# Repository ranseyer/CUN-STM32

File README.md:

View this project on [CADLAB.io](https://cadlab.io/project/1060). 

# CUN-STM32
The MAPLE-CUL is an ARM based RF Transceiver w/wo LAN for 433 or 868 MHz

- based on the STM32 / MAPLE Microcontroller
- Up to 4 Transceiver-Modules
- 2 Free UARTs for other AddOns / Transceiver or so
- 1 UART for WLAN Connection or debugging

-a lot of HW-AddOns are availble

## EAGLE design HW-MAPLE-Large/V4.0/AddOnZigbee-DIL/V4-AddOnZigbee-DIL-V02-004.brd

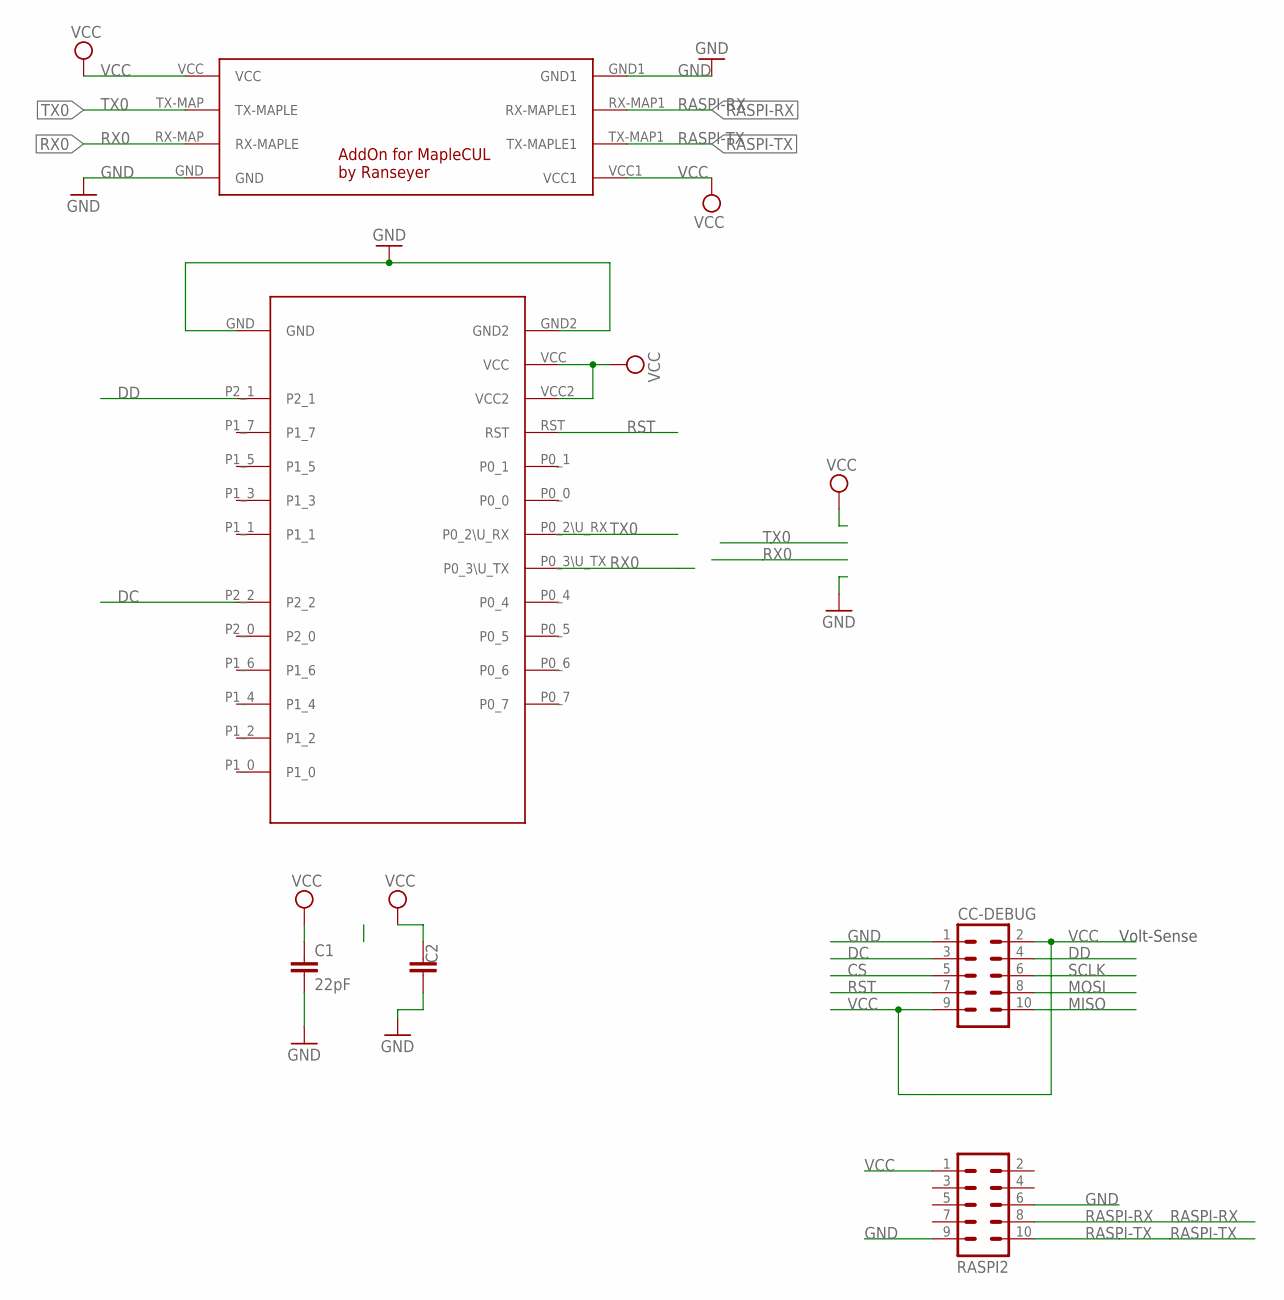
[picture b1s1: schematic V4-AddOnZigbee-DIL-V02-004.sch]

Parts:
C1: 22pF; C0805
C2: C-EUC1812; C1812
CC-DEBUG: CONN_05X2SHD_LOCK; 2X5-SHROUDED_LOCK
RASPI2: MA05-2
U$1: MAPLE-CUL-ADDON-V01; MAPLE-CUL-V01
U$3: CC2530_MODULE; CC2530_DIL

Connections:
CS: CC-DEBUG.5
DC: CC-DEBUG.3, U$3.P2_2
DD: CC-DEBUG.4, U$3.P2_1
GND: C1.2, C2.1, CC-DEBUG.1, RASPI2.6, RASPI2.9, U$1.GND, U$1.GND1, U$3.GND, U$3.GND2
MISO: CC-DEBUG.10
MOSI: CC-DEBUG.8
RASPI-RX: RASPI2.8, U$1.RX-MAP1 (RX-MAPLE1)
RASPI-TX: RASPI2.10, U$1.TX-MAP1 (TX-MAPLE1)
RST: CC-DEBUG.7, U$3.RST
RX0: U$1.RX-MAP (RX-MAPLE), U$3.P0_3\U_TX
SCLK: CC-DEBUG.6
TX0: U$1.TX-MAP (TX-MAPLE), U$3.P0_2\U_RX
VCC: C1.1, C2.2, CC-DEBUG.2, CC-DEBUG.9, RASPI2.1, U$1.VCC, U$1.VCC1, U$3.VCC, U$3.VCC2

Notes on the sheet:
Volt-Sense

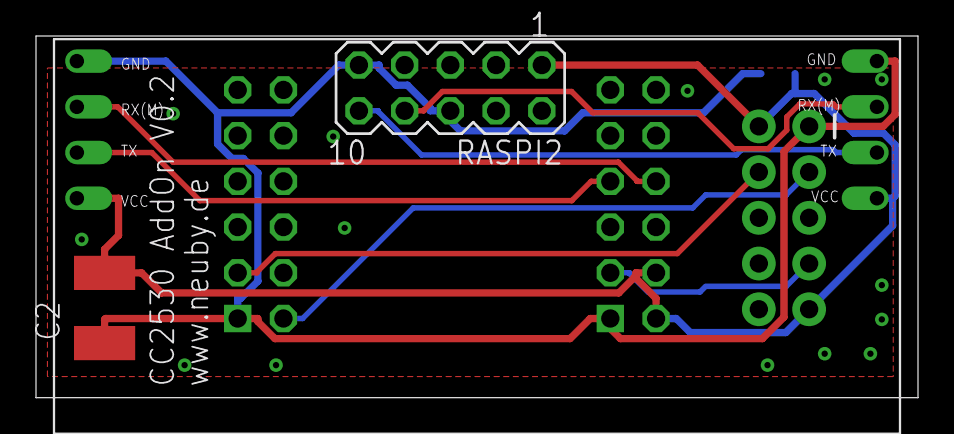
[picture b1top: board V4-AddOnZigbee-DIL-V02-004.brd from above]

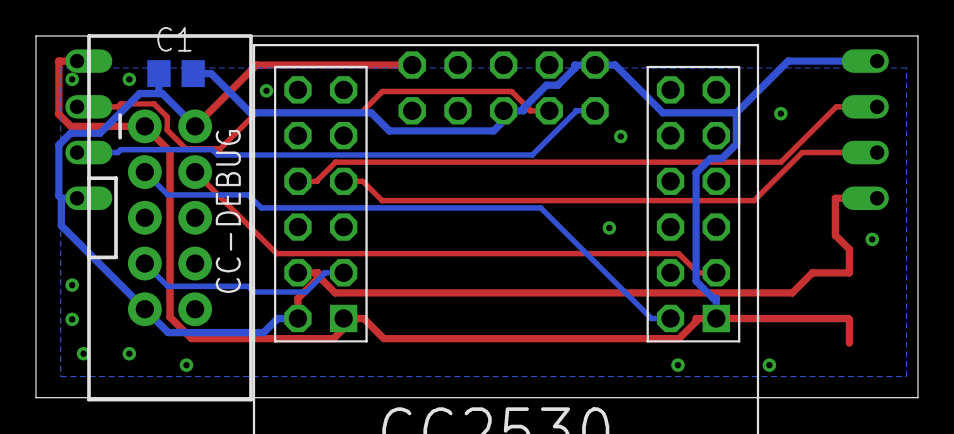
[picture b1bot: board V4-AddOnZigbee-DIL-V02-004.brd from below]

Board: 2 copper layers, 49.0 x 20.1 mm, 6 parts (3 on the bottom side), 9 nets.

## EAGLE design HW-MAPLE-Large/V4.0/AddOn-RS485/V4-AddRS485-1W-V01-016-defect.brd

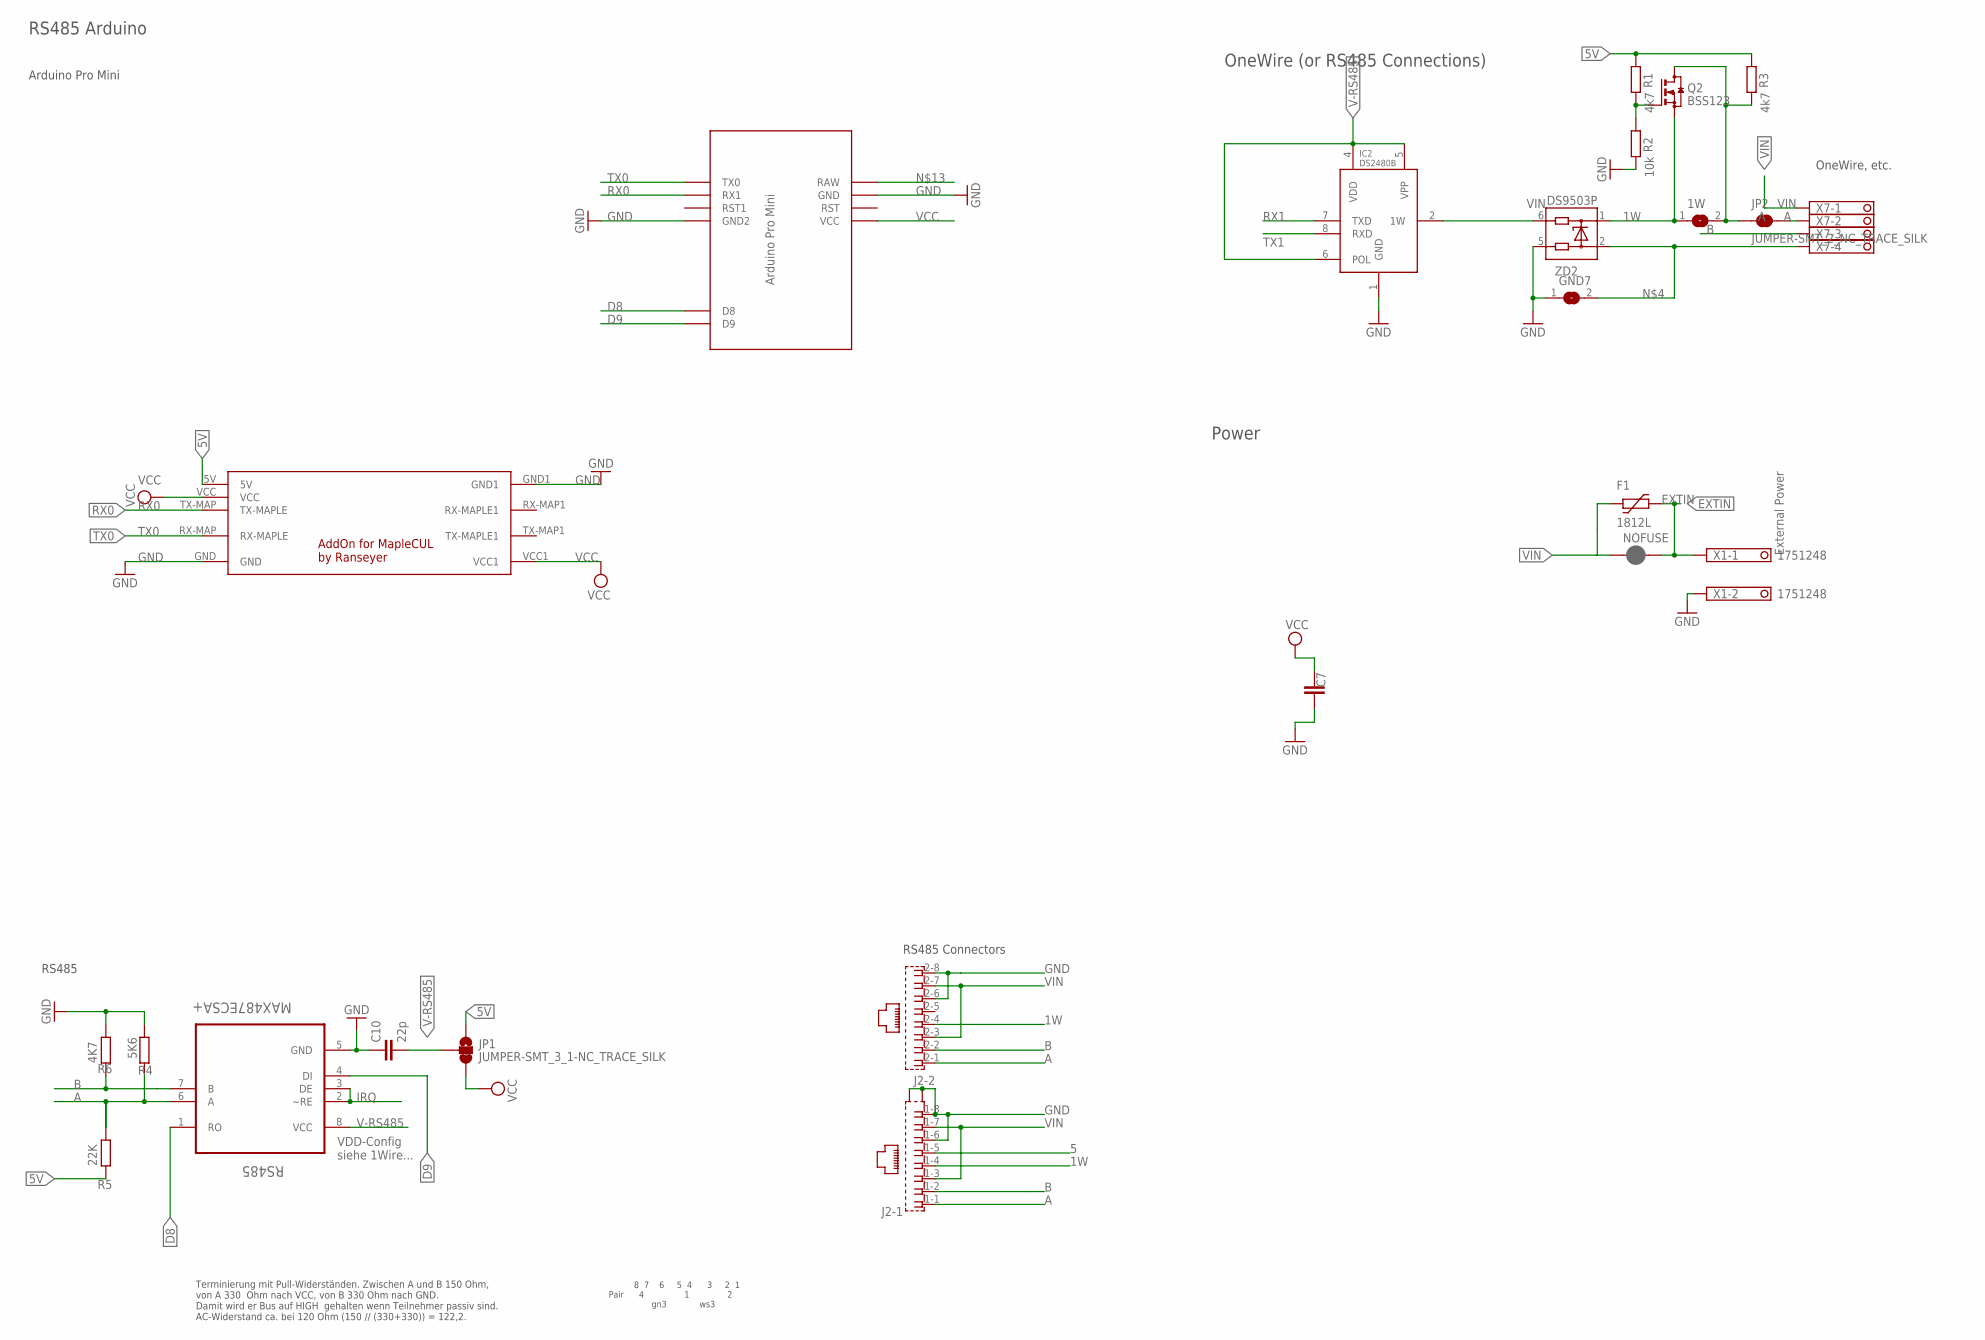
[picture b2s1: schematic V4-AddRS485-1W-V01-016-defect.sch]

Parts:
1W: SJ
C7: C-EUC1812; C1812
C10: 22p; C0805
F1: 1812L
GND7: SJ
IC2: DS2480B; SO08
J2: RJ45_2X_S
JP1: JUMPER-SMT_3_1-NC_TRACE_SILK; SMT-JUMPER_3_1-NC_TRACE_SILK
JP2: JUMPER-SMT_2_NC_TRACE_SILK; SMT-JUMPER_2_NC_TRACE_SILK
NOFUSE: JUMPER-SMT_2_NC_PASTE_NO-SILK; SMT-JUMPER_2_NC_PASTE_NO-SILK
Q2: BSS123; SOT23
R1, R3: 4k7; R0805
R2: 10k; R0805
R4: 5K6; R0805
R5: 22K; R0805
R6: 4K7; R0805
RS485: MAX487ECSA+; SOIC127P600X175-8N
U$2: MAPLE-CUL-ADDON-V01; MAPLE-CUL-V01
U$3: MARTIN-PRO-MINI-RS485
X1: 1751248
X7: 1751264
ZD2: DS9503P; TSOC6

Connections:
1W: 1W.1, J2.1-4 (4), J2.2-4 (4), Q2.2 (S), ZD2.1
5: J2.1-5 (5)
5V: JP1.1, R1.1, R3.1, R5.1, U$2.5V
A: 1W.2, J2.1-1 (1), J2.2-1 (1), JP2.1, JP2.2, Q2.3 (D), R3.2, R4.2, R5.2, RS485.6 (A), X7.2
B: J2.1-2 (2), J2.2-2 (2), R6.1, RS485.7 (B), X7.3
D8: RS485.1 (RO), U$3.D8
D9: RS485.4 (DI), U$3.D9
EXTIN: F1.P$2 (2), NOFUSE.2, X1.1
GND: C7.1, C10.1, GND7.1, IC2.1 (GND), J2.1-6 (6), J2.1-8 (8), J2.2-6 (6), J2.2-8 (8), J2.G1 (S2), J2.G3 (S1), R2.2, R4.1, R6.2, RS485.5 (GND), U$2.GND, U$2.GND1, U$3.GND, U$3.GND1 (GND2), X1.2, ZD2.5
IRQ: RS485.2 (~RE), RS485.3 (DE)
unnamed: C10.2, JP1.2
unnamed: IC2.2 (1W), ZD2.6
unnamed: GND7.2, X7.4, ZD2.2
unnamed: Q2.1 (G), R1.2, R2.1
RX0: U$2.TX-MAP (TX-MAPLE), U$3.RX1
RX1: IC2.7 (TXD)
TX0: U$2.RX-MAP (RX-MAPLE), U$3.TX0
TX1: IC2.8 (RXD)
V-RS485: IC2.4 (VDD), IC2.5 (VPP), IC2.6 (POL), RS485.8 (VCC)
VCC: C7.2, JP1.3, U$2.VCC, U$2.VCC1, U$3.VCC
VIN: F1.P$1 (1), J2.1-3 (3), J2.1-7 (7), J2.2-3 (3), J2.2-7 (7), NOFUSE.1, X7.1

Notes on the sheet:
External Power
8 7 6 5 4 3 2 1 Pair 4 1 2 gn3 ws3
RS485 Connectors
OneWire, etc.
Arduino Pro Mini
RS485
VDD-Config siehe 1Wire...
Terminierung mit Pull-Widerständen. Zwischen A und B 150 Ohm, von A 330 Ohm nach VCC, von B 330 Ohm nach GND. Damit wird er Bus auf HIGH gehalten wenn Teilnehmer passiv sind. AC-Widerstand ca. bei 120 Ohm (150 // (330+330)) = 122,2.
OneWire (or RS485 Connections)
RS485 Arduino
Power

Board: 2 copper layers, 23 parts (4 on the bottom side), 18 nets, no tracks yet.

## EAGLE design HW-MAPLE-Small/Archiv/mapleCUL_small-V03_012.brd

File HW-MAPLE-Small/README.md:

Cases: 

https://www.thingiverse.com/thing:4290984

https://www.thingiverse.com/thing:4286521

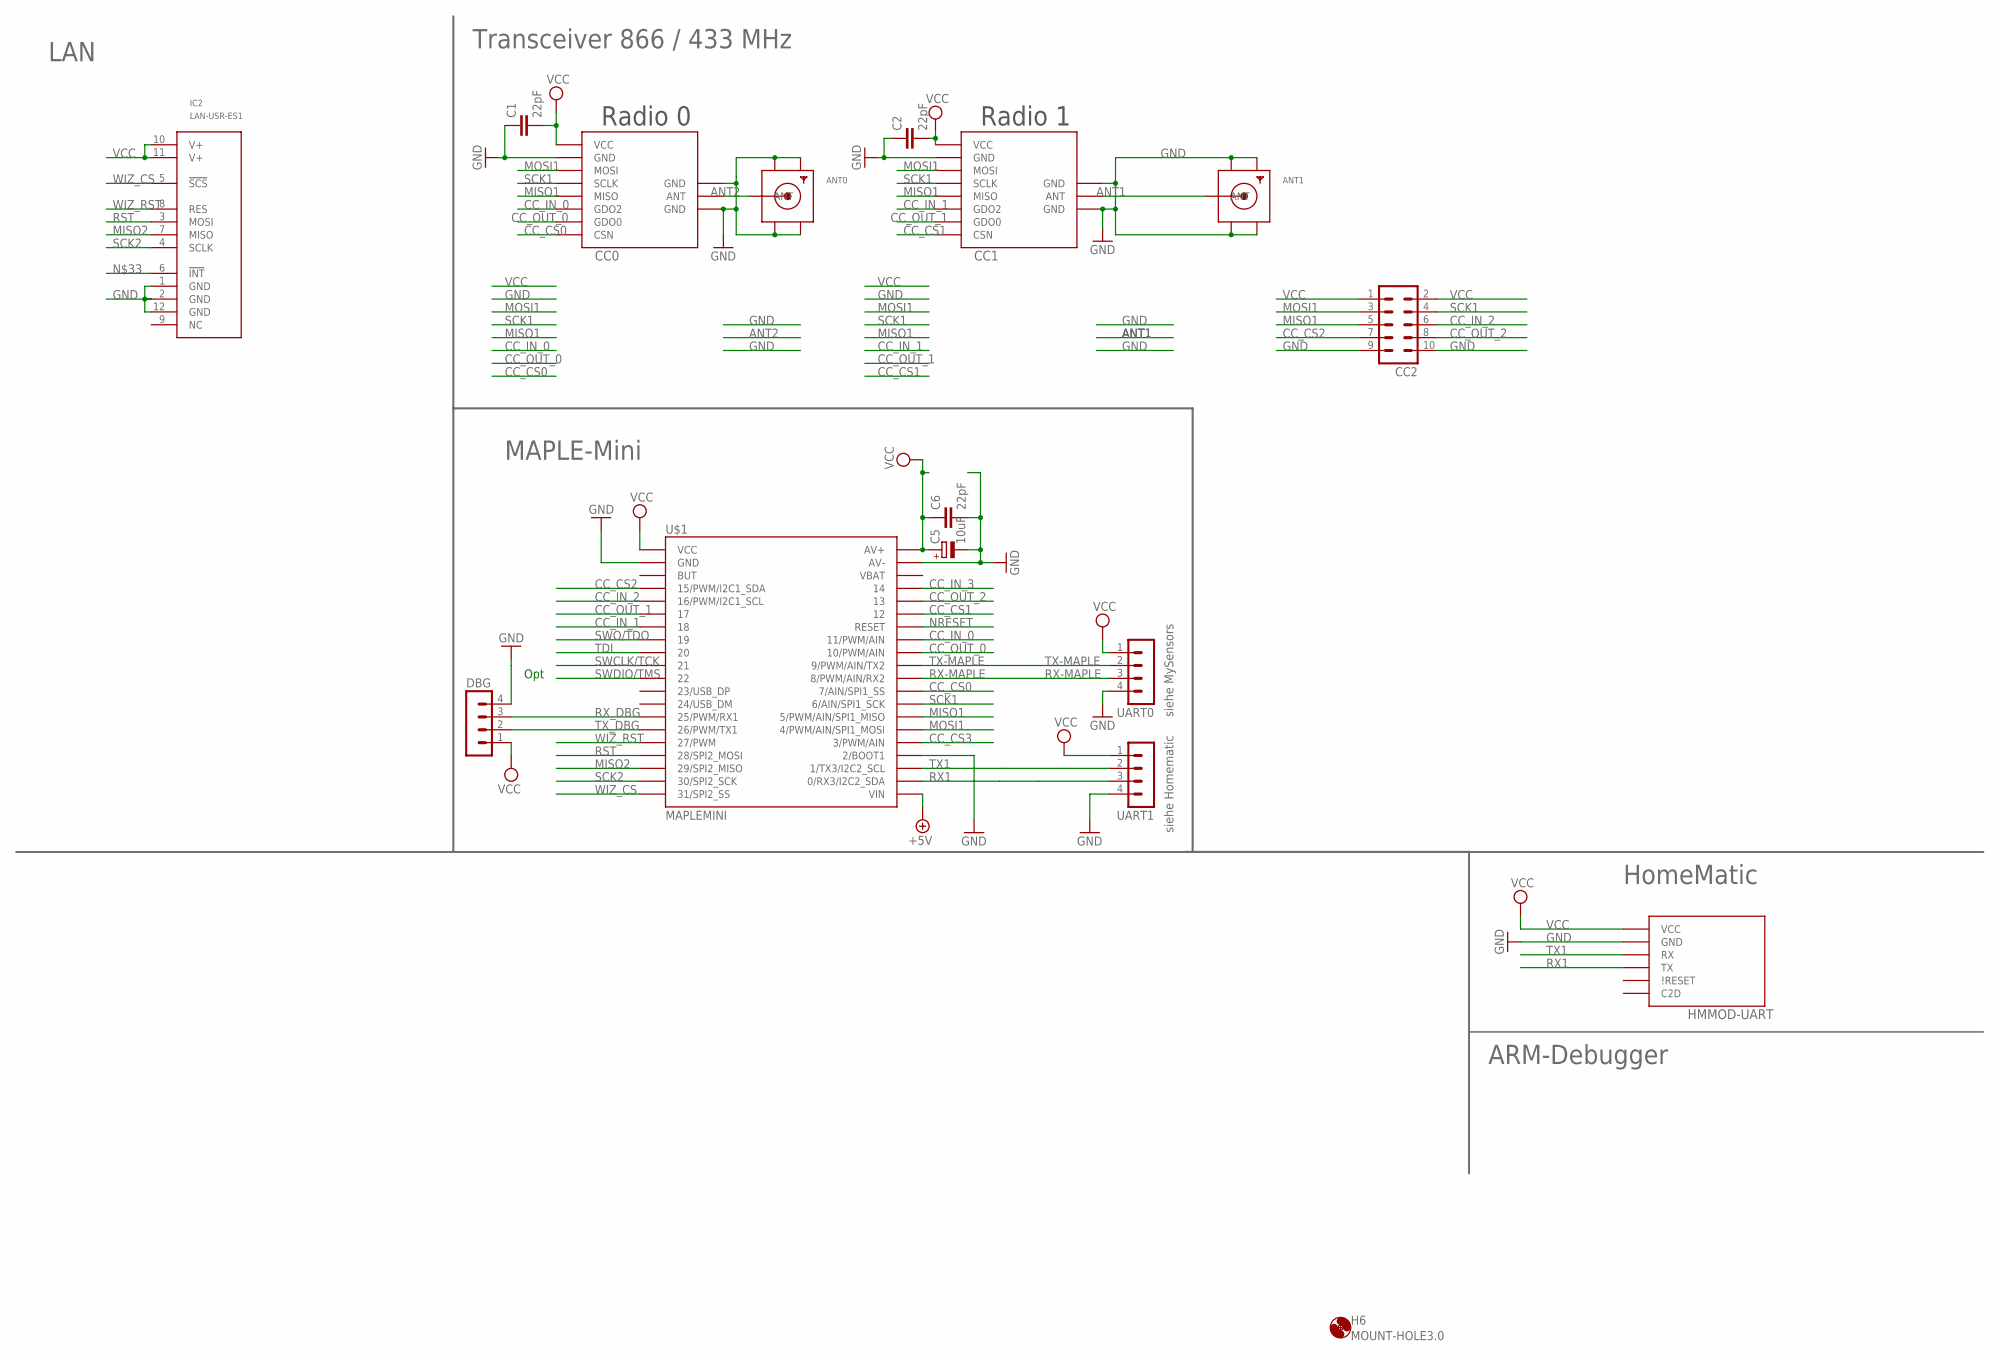
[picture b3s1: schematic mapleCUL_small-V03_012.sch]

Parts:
ANT0, ANT1: SMACONNECTOR_EDGE_UFL; SMA_EDGELAUNCH_UFL
C1, C2, C6: 22pF; C0805
C5: 10uF; R/2012-12W
CC0: CC1101; CC1101_MODULE1_SMD
CC1: CC1101_MODULE1SMD; CC1101_MODULE1_SMD
CC2: MA05-2
DBG: MA04-1
H6: MOUNT-HOLE3.0; 3,0
HMMOD-UART: HM-MOD-UARTDIL; HM-MOD-UART-DIL
IC2: LAN-USR-ES1; USR-ES1
U$1: MAPLEMINI; 20-DIP
UART0, UART1: MA04-1

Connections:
+5V: U$1.21 (VIN)
ANT1: ANT1.P (ANT), CC1.ANT
ANT2: ANT0.P (ANT), CC0.ANT
CC_CS0: CC0.CSN, U$1.29 (7/AIN/SPI1_SS)
CC_CS1: CC1.CSN, U$1.35 (12)
CC_CS2: CC2.7, U$1.4 (15/PWM/I2C1_SDA)
CC_CS3: U$1.25 (3/PWM/AIN)
CC_IN_0: CC0.GDO2, U$1.33 (11/PWM/AIN)
CC_IN_1: CC1.GDO2, U$1.7 (18)
CC_IN_2: CC2.6, U$1.5 (16/PWM/I2C1_SCL)
CC_IN_3: U$1.37 (14)
CC_OUT_0: CC0.GDO0, U$1.32 (10/PWM/AIN)
CC_OUT_1: CC1.GDO0, U$1.6 (17)
CC_OUT_2: CC2.8, U$1.36 (13)
GND: ANT0.GND@1 (GND1), ANT0.GND@2 (GND2), ANT0.GND@3 (GND3), ANT0.GND@4 (GND4), ANT1.GND@1 (GND1), ANT1.GND@2 (GND2), ANT1.GND@3 (GND3), ANT1.GND@4 (GND4), C1.1, C2.1, C5.-, C6.2, CC0.GND@0 (GND), CC0.GND@1 (GND), CC0.GND@2 (GND), CC1.GND@0 (GND), CC1.GND@1 (GND), CC1.GND@2 (GND), CC2.9, CC2.10, DBG.4, HMMOD-UART.2 (GND), IC2.1 (GND), IC2.2 (GND), IC2.12 (GND), U$1.2 (GND), U$1.24 (2/BOOT1), U$1.39 (AV-), UART0.4, UART1.4
MISO1: CC0.MISO, CC1.MISO, CC2.5, U$1.27 (5/PWM/AIN/SPI1_MISO)
MISO2: IC2.7 (MISO), U$1.18 (29/SPI2_MISO)
MOSI1: CC0.MOSI, CC1.MOSI, CC2.3, U$1.26 (4/PWM/AIN/SPI1_MOSI)
NRESET: U$1.34 (RESET)
RST: IC2.3 (MOSI), U$1.17 (28/SPI2_MOSI)
RX1: HMMOD-UART.5 (TX), U$1.22 (0/RX3/I2C2_SDA), UART1.3
RX-MAPLE: U$1.30 (8/PWM/AIN/RX2), UART0.3
RX_DBG: DBG.3, U$1.14 (25/PWM/RX1)
SCK1: CC0.SCLK, CC1.SCLK, CC2.4, U$1.28 (6/AIN/SPI1_SCK)
SCK2: IC2.4 (SCLK), U$1.19 (30/SPI2_SCK)
SWCLK/TCK: U$1.10 (21)
SWDIO/TMS: U$1.11 (22)
SWO/TDO: U$1.8 (19)
TDI: U$1.9 (20)
TX1: HMMOD-UART.6 (RX), U$1.23 (1/TX3/I2C2_SCL), UART1.2
TX-MAPLE: U$1.31 (9/PWM/AIN/TX2), UART0.2
TX_DBG: DBG.2, U$1.15 (26/PWM/TX1)
VCC: C1.2, C2.2, C5.+, C6.1, CC0.VCC, CC1.VCC, CC2.1, CC2.2, DBG.1, HMMOD-UART.1 (VCC), IC2.10 (V+), IC2.11 (V+), U$1.1 (VCC), U$1.40 (AV+), UART0.1, UART1.1
WIZ_CS: IC2.5 (!SCS!), U$1.20 (31/SPI2_SS)
WIZ_RST: IC2.8 (RES), U$1.16 (27/PWM)

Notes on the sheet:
Radio 1
Radio 0
Opt
siehe Homematic
siehe MySensors
HomeMatic
MAPLE-Mini
Transceiver 866 / 433 MHz
LAN
ARM-Debugger

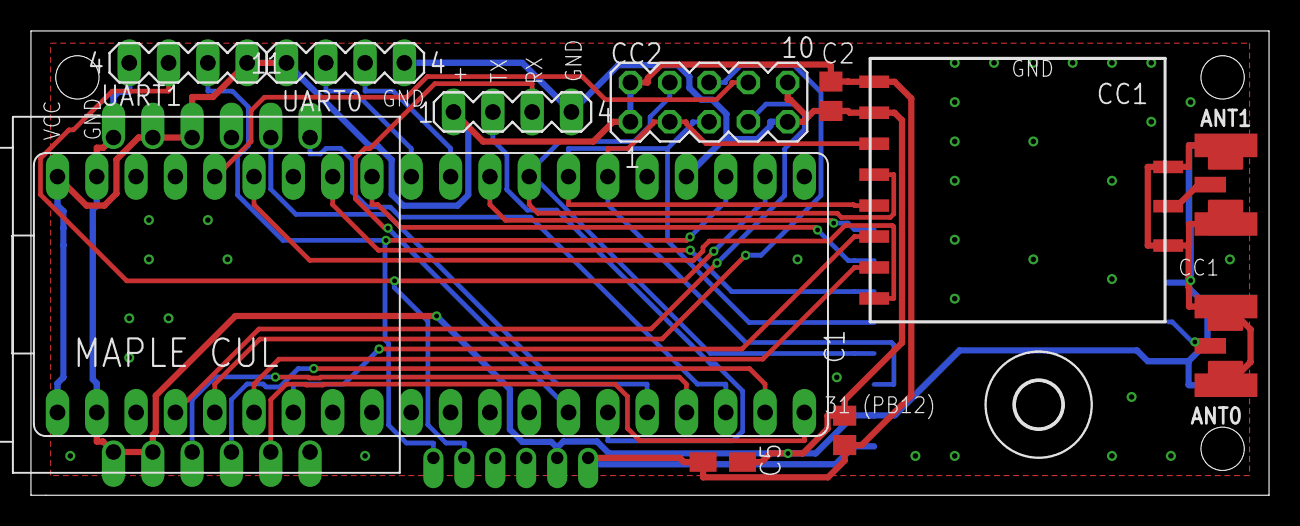
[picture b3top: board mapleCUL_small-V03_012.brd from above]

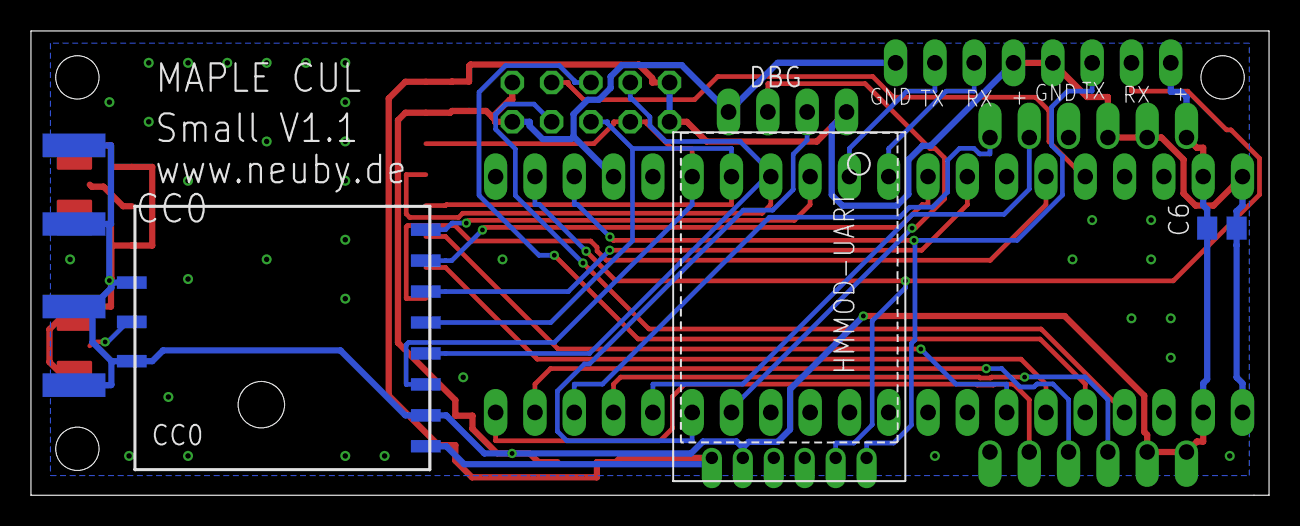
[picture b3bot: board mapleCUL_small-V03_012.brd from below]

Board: 2 copper layers, 80.0 x 30.0 mm, 16 parts (3 on the bottom side), 27 nets.

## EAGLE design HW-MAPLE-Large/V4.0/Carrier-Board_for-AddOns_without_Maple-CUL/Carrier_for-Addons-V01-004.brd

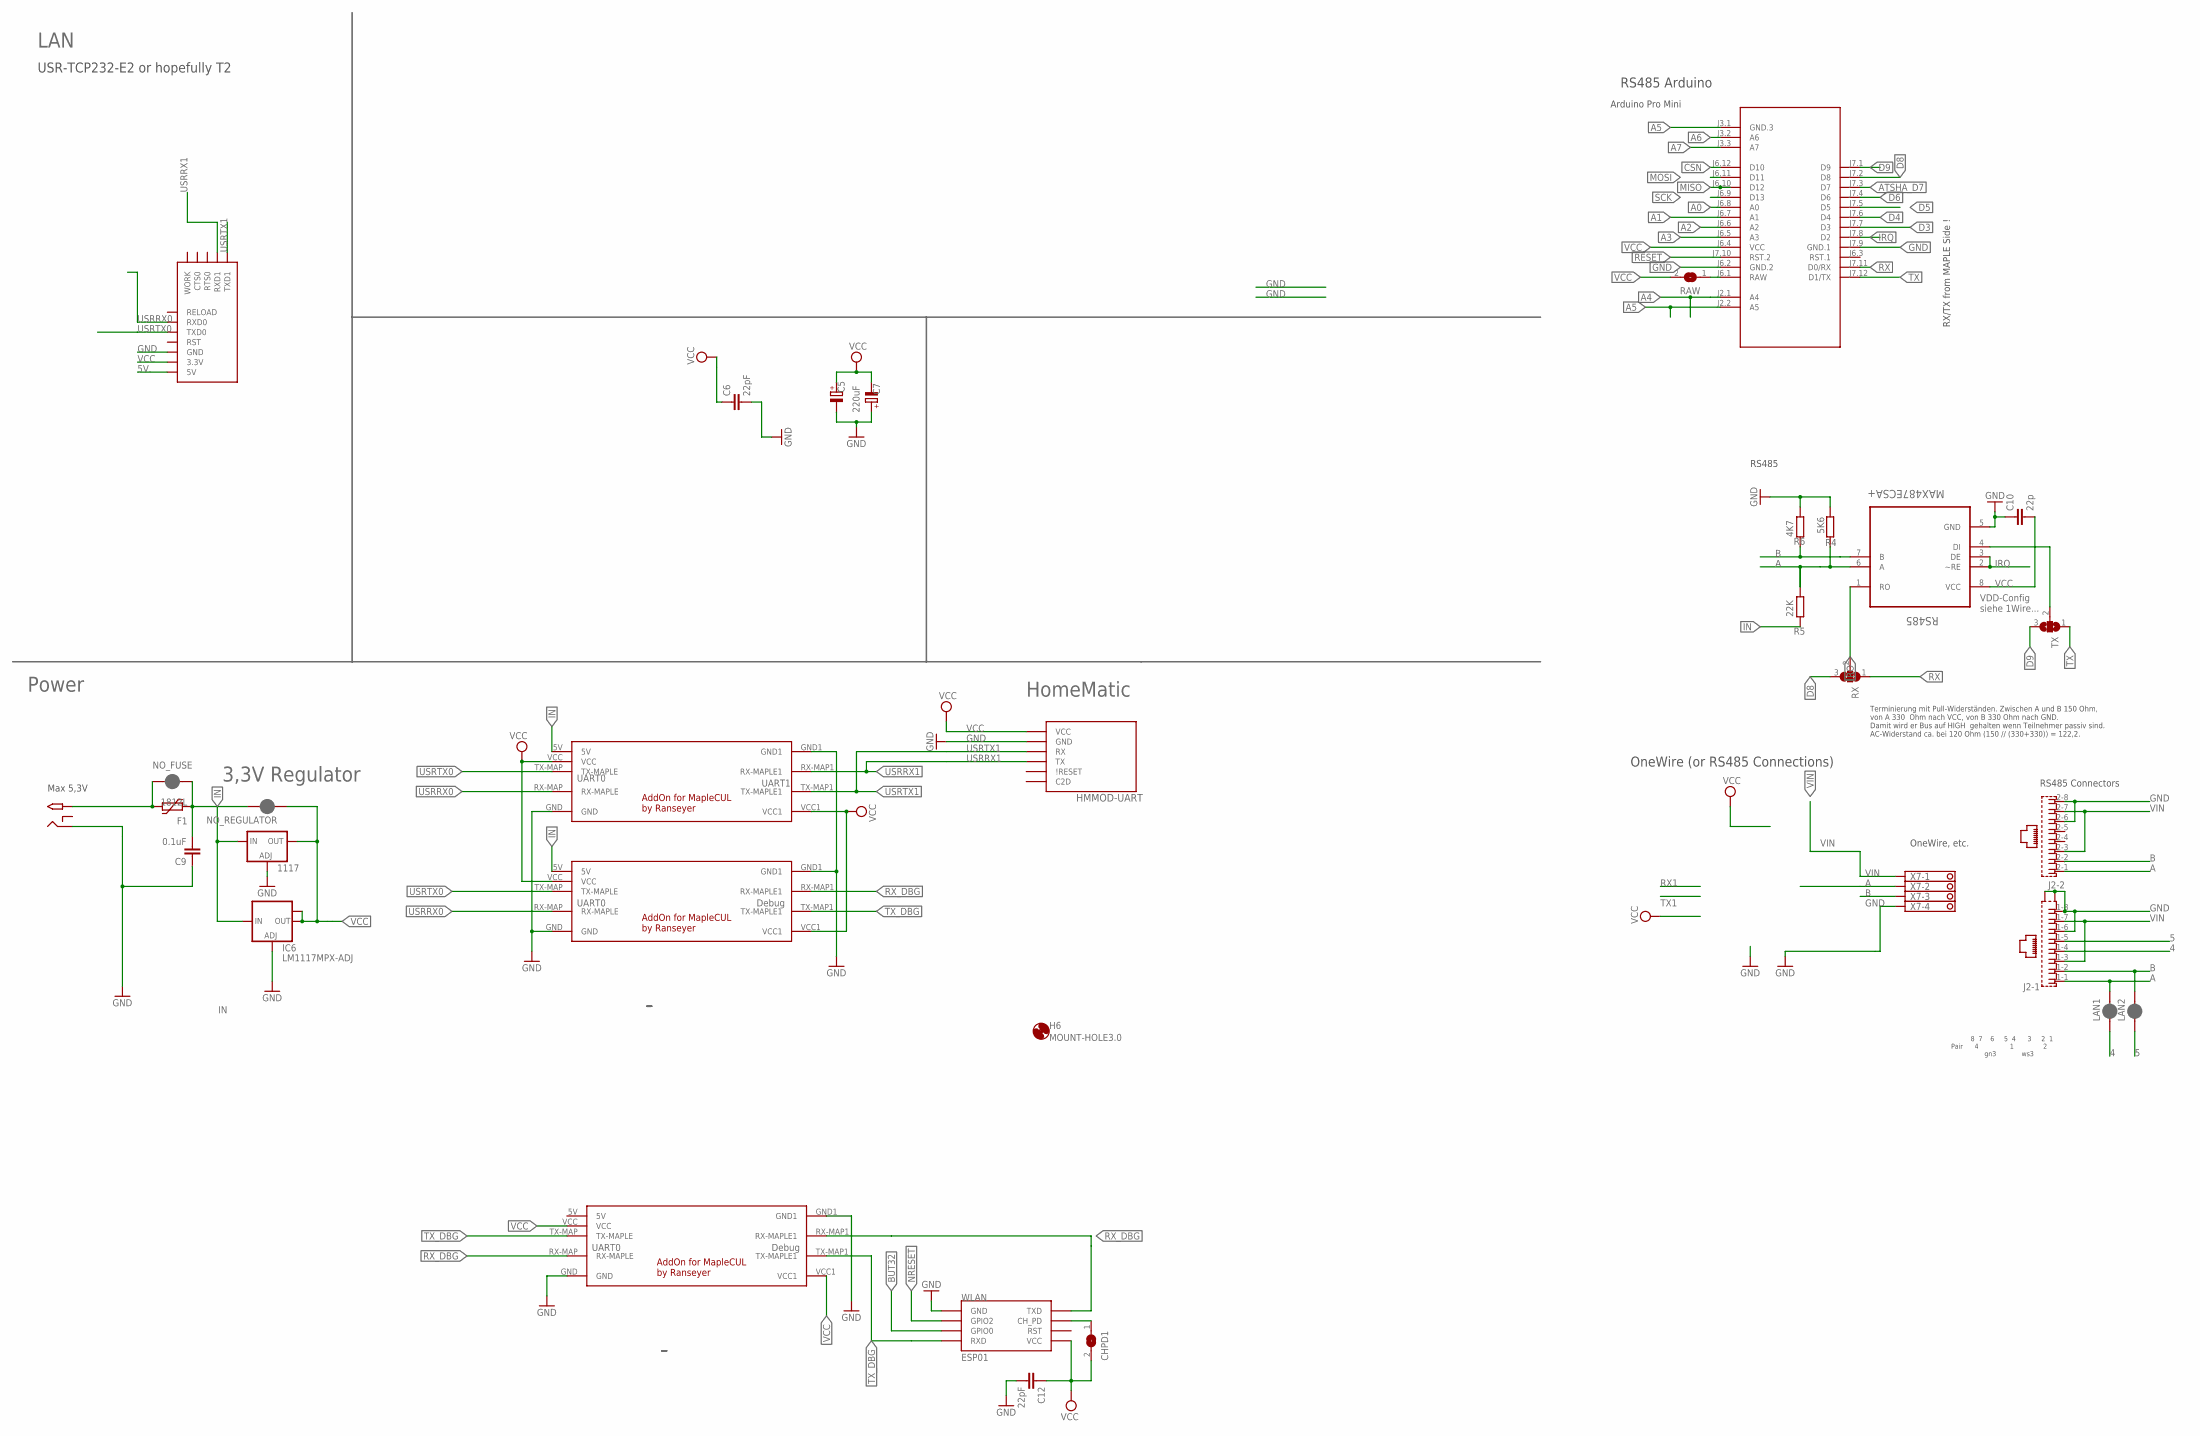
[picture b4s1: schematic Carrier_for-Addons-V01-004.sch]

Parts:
1117: LD117ADT50TR; DPACK
C5: 220uF; E5-8,5
C6, C12: 22pF; C0805
C7: CPOL-EUSMCE; SMC_E
C9: 0.1uF; C1206
C10: 22p; C0805
CHPD1: SJ
F1: 1812L
H6: MOUNT-HOLE3.0; 3,0
HMMOD-UART: HM-MOD-UARTDIL; HM-MOD-UART-DIL
IC6: LM1117MPX-ADJ; SOT223
J2: RJ45_2X_S
LAN1, LAN2: JUMPER-SMT_2_NC_PASTE_SILK; SMT-JUMPER_2_NC_PASTE_SILK
M1: ARDUINO-PRO-MINI-3.3V#NP; ARDUINO-PRO-MINI#NP
NO_FUSE: JUMPER-SMT_2_NC_PASTE_NO-SILK; SMT-JUMPER_2_NC_PASTE_NO-SILK
NO_REGULATOR: JUMPER-SMT_2_NC_PASTE_NO-SILK; SMT-JUMPER_2_NC_PASTE_NO-SILK
R4: 5K6; R0805
R5: 22K; R0805
R6: 4K7; R0805
RAW: SJ
RS485: MAX487ECSA+; SOIC127P600X175-8N
RX: SJ2W; SJ_2
TX: SJ2W; SJ_2
U$1, U$3, U$4: MAPLE-CUL-ADDON-V01; MAPLE-CUL-V01
U$2: 2.1MMJACKTHM; PJ-102A
U$5: USR-TCP232-E2
WLAN: ESP01
X7: 1751264

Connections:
4: J2.1-4 (4), LAN1.1
5: J2.1-5 (5), LAN2.1
5V.: U$5.5V
A: J2.1-1 (1), J2.2-1 (1), LAN1.2, R4.2, R5.2, RS485.6 (A), X7.2
A0: M1.J6.8 (A0)
A1: M1.J6.7 (A1)
A2: M1.J6.6 (A2)
A3: M1.J6.5 (A3)
A4: M1.J2.1 (A4)
A5: M1.J2.2 (A5), M1.J3.1 (GND.3)
A6: M1.J3.2 (A6)
A7: M1.J3.3 (A7)
ATSHA_D7: M1.J7.3 (D7)
B: J2.1-2 (2), J2.2-2 (2), LAN2.2, R6.1, RS485.7 (B), X7.3
BUT32: WLAN.GPIO0
CSN: M1.J6.12 (D10)
D3: M1.J7.7 (D3)
D4: M1.J7.6 (D4)
D5: M1.J7.5 (D5)
D6: M1.J7.4 (D6)
D8: M1.J7.2 (D8), RX.3
D9: M1.J7.1 (D9), TX.3
DI1: RS485.4 (DI), TX.2
GND: 1117.1 (ADJ), C5.-, C6.2, C7.+, C9.1, C10.1, C12.2, HMMOD-UART.2 (GND), IC6.1 (ADJ), J2.1-6 (6), J2.1-8 (8), J2.2-6 (6), J2.2-8 (8), J2.G1 (S2), J2.G3 (S1), M1.J6.2 (GND.2), M1.J7.9 (GND.1), R4.1, R6.2, RS485.5 (GND), U$1.GND, U$1.GND1, U$2.RING, U$3.GND, U$3.GND1, U$4.GND, U$4.GND1, U$5.GND, WLAN.GND, X7.4
IN: 1117.3 (IN), C9.2, F1.P$1 (1), IC6.3 (IN), NO_FUSE.1, NO_REGULATOR.2, R5.1, U$3.5V, U$4.5V
IRQ: M1.J7.8 (D2), RS485.2 (~RE), RS485.3 (DE)
MISO: M1.J6.10 (D12)
MOSI: M1.J6.11 (D11)
unnamed: CHPD1.1, WLAN.CH_PD
NRESET: WLAN.GPIO2
RAW1: M1.J6.1 (RAW), RAW.1
RESET: M1.J7.10 (RST.2)
RO: RS485.1 (RO), RX.2
RX: M1.J7.11 (D0/RX), RX.1
RX_DBG: U$1.RX-MAP (RX-MAPLE), U$1.RX-MAP1 (RX-MAPLE1), U$4.RX-MAP1 (RX-MAPLE1), WLAN.TX (TXD)
SCK: M1.J6.9 (D13)
TX: M1.J7.12 (D1/TX), TX.1
TX_DBG: U$1.TX-MAP (TX-MAPLE), U$1.TX-MAP1 (TX-MAPLE1), U$4.TX-MAP1 (TX-MAPLE1), WLAN.RX (RXD)
USRRX0: U$3.RX-MAP (RX-MAPLE), U$4.RX-MAP (RX-MAPLE), U$5.RXD0
USRRX1: HMMOD-UART.5 (TX), U$3.RX-MAP1 (RX-MAPLE1), U$5.RXD1
USRTX0: U$3.TX-MAP (TX-MAPLE), U$4.TX-MAP (TX-MAPLE), U$5.TXD0
USRTX1: HMMOD-UART.6 (RX), U$3.TX-MAP1 (TX-MAPLE1), U$5.TXD1
VCC: 1117.4 (OUT), C5.+, C6.1, C7.-, C10.2, C12.1, CHPD1.2, HMMOD-UART.1 (VCC), IC6.2 (OUT), IC6.TAB (OUT1), M1.J6.4 (VCC), NO_REGULATOR.1, RAW.2, RS485.8 (VCC), U$1.VCC, U$1.VCC1, U$3.VCC, U$3.VCC1, U$4.VCC, U$4.VCC1, U$5.3.3V, WLAN.VCC
VIN: F1.P$2 (2), J2.1-3 (3), J2.1-7 (7), J2.2-3 (3), J2.2-7 (7), NO_FUSE.2, U$2.TIP, X7.1

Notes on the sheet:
Power
HomeMatic
LAN
UART0
Debug
UART1
RX/TX from MAPLE Side !
8 7 6 5 4 3 2 1 Pair 4 1 2 gn3 ws3
RS485 Connectors
OneWire, etc.
Arduino Pro Mini
RS485
VDD-Config siehe 1Wire...
Terminierung mit Pull-Widerständen. Zwischen A und B 150 Ohm, von A 330 Ohm nach VCC, von B 330 Ohm nach GND. Damit wird er Bus auf HIGH gehalten wenn Teilnehmer passiv sind. AC-Widerstand ca. bei 120 Ohm (150 // (330+330)) = 122,2.
OneWire (or RS485 Connections)
USR-TCP232-E2 or hopefully T2
RS485 Arduino
Max 5,3V
3,3V Regulator

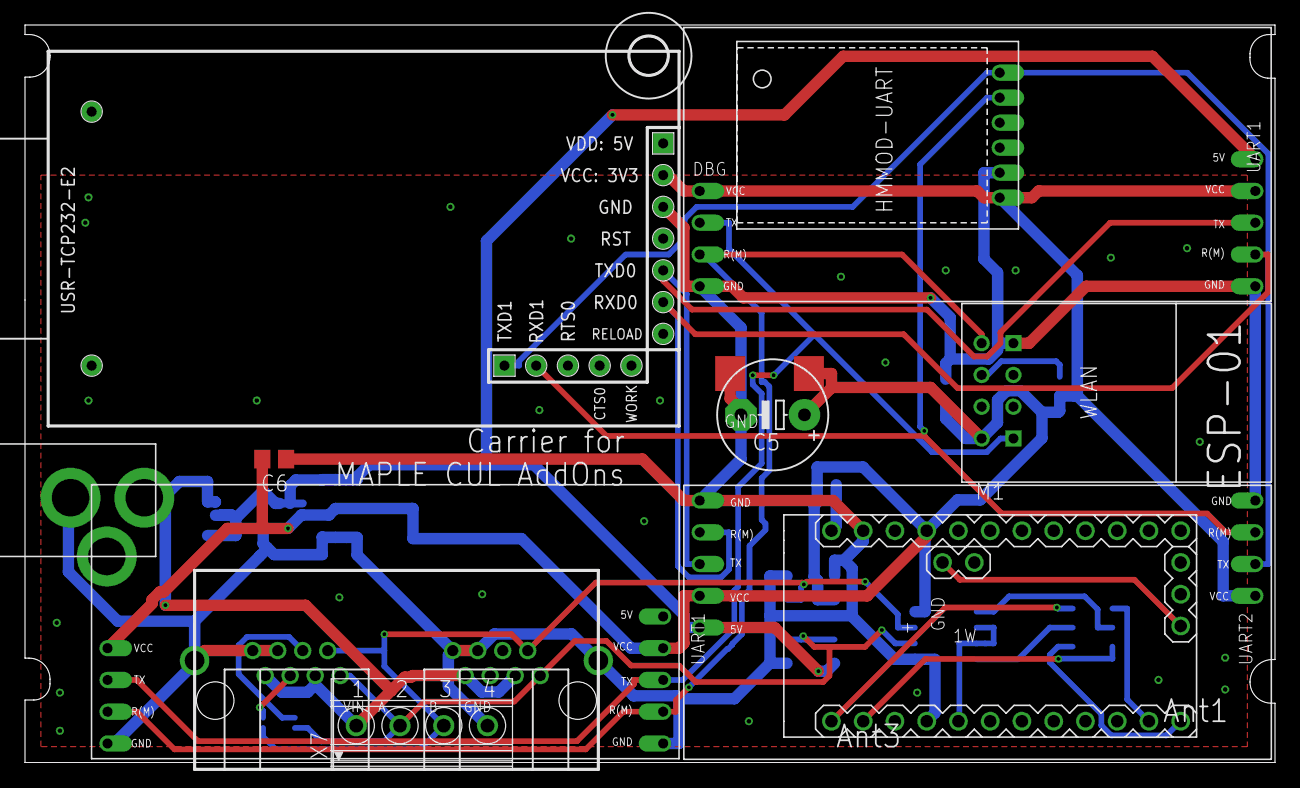
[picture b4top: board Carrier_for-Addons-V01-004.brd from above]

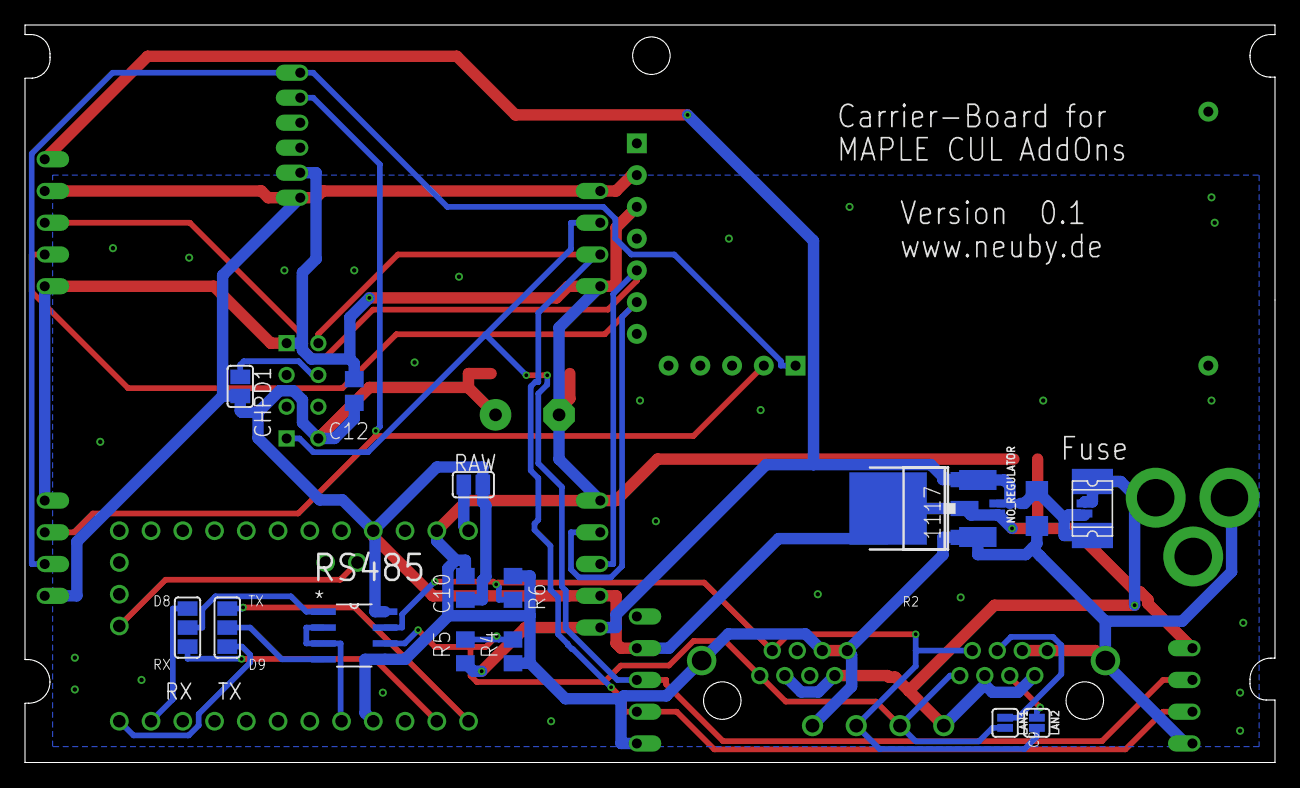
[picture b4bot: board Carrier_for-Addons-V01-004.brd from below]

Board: 2 copper layers, 100.0 x 59.0 mm, 32 parts (18 on the bottom side), 24 nets.

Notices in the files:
parts and their libraries:
SparkFun-Jumpers: Licensing: Creative Commons ShareAlike 4.0 International - https://creativecommons.org/licenses/by-sa/4.0
microbuilder: This work is placed in the public domain, and may be freely used for commercial and non-commercial work with the following conditions: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
